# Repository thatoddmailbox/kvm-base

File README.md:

# kvm-base

The main board for the [open-source HDMI KVM switch I built](https://github.com/thatoddmailbox/kvm#kvm). Contains HDMI and USB switch ICs, allowing you to share two monitors and four USB devices between three different computers.

This is a 1.6mm four layer PCB, designed for JLCPCB's [JLC7628](https://jlcpcb.com/quote/pcbOrderFaq/PCB%20Stackup) impedance-controlled stackup. It most likely will not work (or will be limited in terms of HDMI performance) on another stackup.

It connects via a PS/2 cable to [kvm-keypad](https://github.com/thatoddmailbox/kvm-keypad)&mdash;however, it does _not_ use the actual PS/2 protocol.

Two [TMDS361B](https://www.ti.com/lit/ds/symlink/tmds361b.pdf) chips are used as HDMI switches, and an [FSUSB74](https://www.onsemi.com/pub/Collateral/FSUSB74-D.pdf) is used as the USB switch.

## Assembly
The full Bill of Materials is linked at the end of the README, and you should get the PCB fabricated at JLCPCB with their impedance-controlled JLC7628 process.

A stencil is probably the easiest way to assemble the board, but it's definitely possible to do so without one, as long as you have a hot air rework station. The trickiest parts to solder are probably the FSUSB74 (QFN with 0.4 mm pitch but no thermal pad) and the TMDS361B (TQFP with 0.5 mm pitch).

The HDMI connectors are also somewhat tricky, given that they are on both sides of the board and also have a relatively fine pitch. However, it's doable with a soldering iron, flux, solder wick, and ideally some form of magnification&mdash;you just have to be careful to ensure the pins are aligned with the footprint on the board before soldering.

## Note on sink-side output stages
Interestingly, the TMDS361B's datasheet pretty clearly states that it's "not intended for source side applications such as external switch boxes", which I probably missed when designing this board.

The consequences of this seem to be that there's little/no ESD protection on the sink side (the monitor output ports), and that the chip has a fairly weak sink-side output stage. That means you probably can't use the output with super long or super cheap cables. The inputs, however, should be fine, since TI claims that the TMDS361B has a "robust TMDS receive stage" that even works with out-of-spec HDMI signals.

Anecdotally, the output does seem to work, but I haven't tested it in that many conditions. This has been tested with a 3 foot HDMI cable going to an Acer EB243YU monitor, using a resolution of 2560 x 1440 at 75 Hz, which is outside of the TMDS361B's spec!

Theoretically, you might be able to work around this by running the output signals to another board with a retimer or redriver, but that's probably somewhat excessive. A future revision should use a different chip and/or integrate a retimer/redriver to the output stage. Unfortunately, it might be somewhat tricky to find an easily accessible HDMI switch chip&mdash;most seem to want you to sign an NDA before getting any documentation.

## Useful links
* [Rev A schematic](./mfg/revA/kvm-base.pdf)
* [Rev A BOM](./mfg/revA/kvm-base.csv)

## Known issues
* TMDS361B's sink-side output stages, as mentioned above
* HDMI ports are too close together -- some cables might be too big to fit
* Some FSUSB74 ports seem to not be working -- this could be a soldering issue
	* Port 2 works perfectly
	* With ports 0 and 1, the computer detects a device but then complains the device is not responding
	* Suspect that probably one of the D+/D- lines is not well connected
* The HPD and DDC lines are switched along with the ports. This means that switching ports will cause the connected source to think the monitor went away, which might not be what you want
	* A future version will probably need to have some sort of EDID cloning/emulation, or have some way to keep the HPD line high after the monitor is connected?
	* There is a workaround: cover the HPD pin (pin 19) of your HDMI cable with tape to block the HPD signal.
		* This workaround means that some sources, like a laptop, might not autodetect your HDMI cable. You'll need to have some way to rescan. On Linux, you can try the command `xrandr --listmonitors`.
		* This might be solvable by cutting the cable open and soldering a 10k resistor between HPD and +5V? That's somewhat extra though
* The device can kinda sorta be powered by a sink&mdash;most likely the ESD diodes in the TMDS361B are backfeeding power on the +5V line.
* The keypad might have some trouble with noise when a PS/2 cable is connected, although it has been worked around in the firmware. A future revision might need a buffer or redriver or something similar? Plain I2C is probably not the best choice for communication between the base and keypad.

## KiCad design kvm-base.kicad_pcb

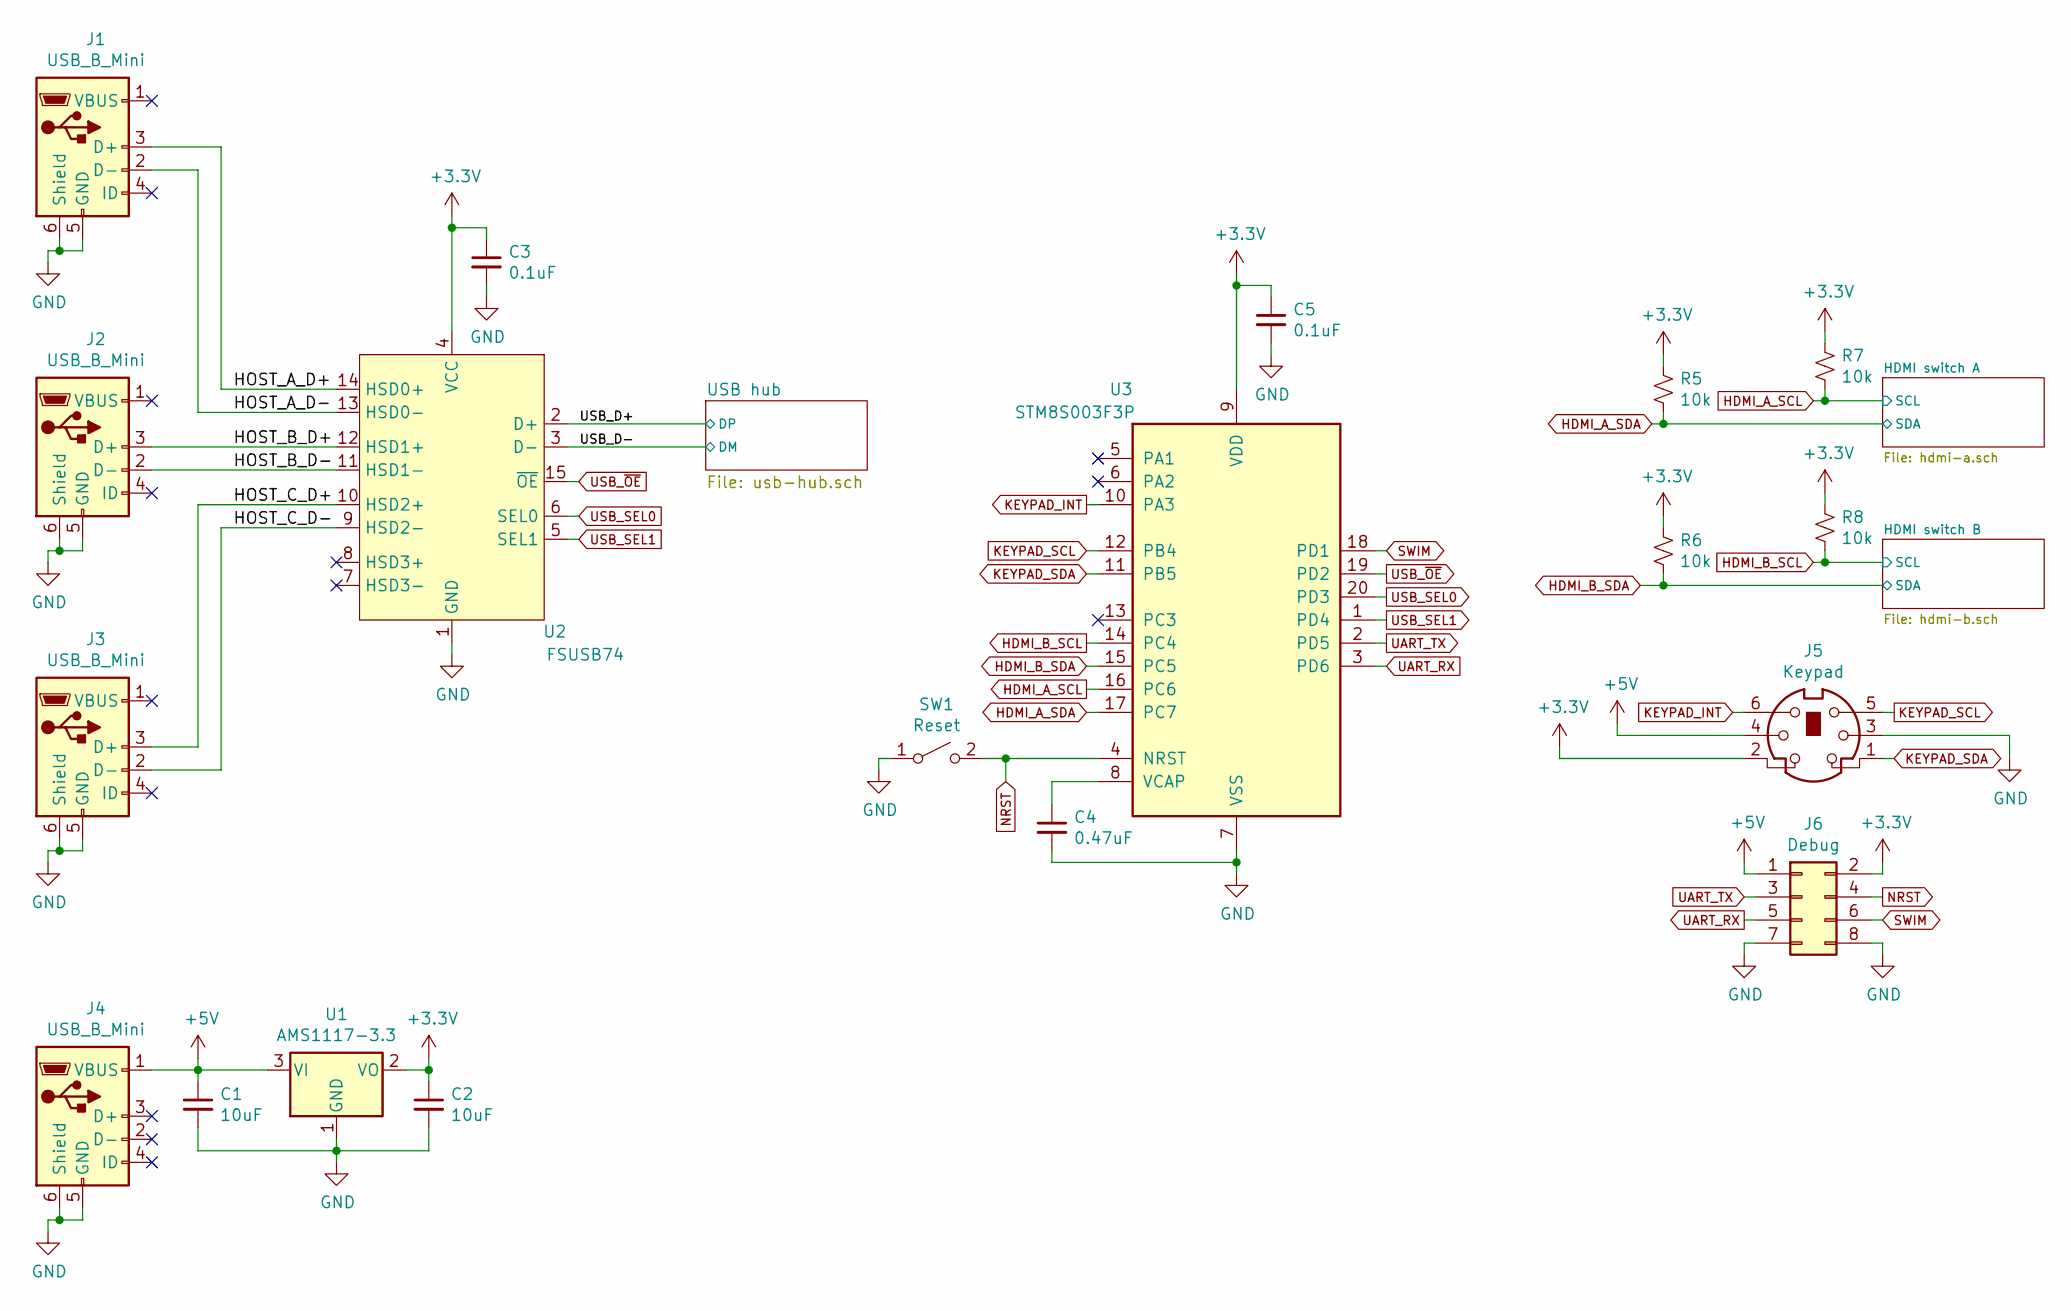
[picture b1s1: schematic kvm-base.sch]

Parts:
C1, C2: 10uF; C_0603_1608Metric_Pad1.05x0.95mm_HandSolder
C3, C5: 0.1uF; C_0603_1608Metric_Pad1.05x0.95mm_HandSolder
C4: 0.47uF; C_0603_1608Metric_Pad1.05x0.95mm_HandSolder
J1, J2, J3, J4: USB_B_Mini; USB_Mini-B_Lumberg_2486_01_Horizontal
J5: Keypad; PS2
J6: Debug; PinSocket_2x04_P2.54mm_Vertical
R5, R6, R7, R8: 10k; R_0603_1608Metric_Pad1.05x0.95mm_HandSolder
SW1: Reset; SW_Push_1P1T_NO_6x6mm_H9.5mm
U1: AMS1117-3.3; SOT-223-3_TabPin2
U2: FSUSB74; UMLP16
U3: STM8S003F3P; TSSOP-20_4.4x6.5mm_P0.65mm

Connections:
+3V3: C2.1, C3.1, C5.1, J5.2, J6.2, R5.1, R6.1, R7.1, R8.1, U1.2 (VO), U2.4 (VCC), U3.9 (VDD); also elsewhere on the board
+5V: C1.1, J4.1 (VBUS), J5.4, J6.1, U1.3 (VI); also elsewhere on the board
/HOST_A_D+: J1.3 (D+), U2.14 (HSD0+)
/HOST_A_D-: J1.2 (D-), U2.13 (HSD0-)
/HOST_B_D+: J2.3 (D+), U2.12 (HSD1+)
/HOST_B_D-: J2.2 (D-), U2.11 (HSD1-)
/HOST_C_D+: J3.3 (D+), U2.10 (HSD2+)
/HOST_C_D-: J3.2 (D-), U2.9 (HSD2-)
/USB_D+: U2.2 (D+); also elsewhere on the board
/USB_D-: U2.3 (D-); also elsewhere on the board
GND: C1.2, C2.2, C3.2, C4.2, C5.2, J1.5 (GND), J1.6 (Shield), J2.5 (GND), J2.6 (Shield), J3.5 (GND), J3.6 (Shield), J4.5 (GND), J4.6 (Shield), J5.3, J6.7, J6.8, SW1.1 (A), U1.1 (GND), U2.1 (GND), U3.7 (VSS); also elsewhere on the board
HDMI_A_SCL: R7.2, U3.16 (PC6); also elsewhere on the board
HDMI_A_SDA: R5.2, U3.17 (PC7); also elsewhere on the board
HDMI_B_SCL: R8.2, U3.14 (PC4); also elsewhere on the board
HDMI_B_SDA: R6.2, U3.15 (PC5); also elsewhere on the board
KEYPAD_INT: J5.6, U3.10 (PA3)
KEYPAD_SCL: J5.5, U3.12 (PB4)
KEYPAD_SDA: J5.1, U3.11 (PB5)
NRST: J6.4, SW1.2 (B), U3.4 (NRST)
unnamed: C4.1, U3.8 (VCAP)
SWIM: J6.6, U3.18 (PD1)
UART_RX: J6.5, U3.3 (PD6)
UART_TX: J6.3, U3.2 (PD5)
USB_SEL0: U2.6 (SEL0), U3.20 (PD3)
USB_SEL1: U2.5 (SEL1), U3.1 (PD4)
USB_~OE: U2.15 (~OE), U3.19 (PD2)

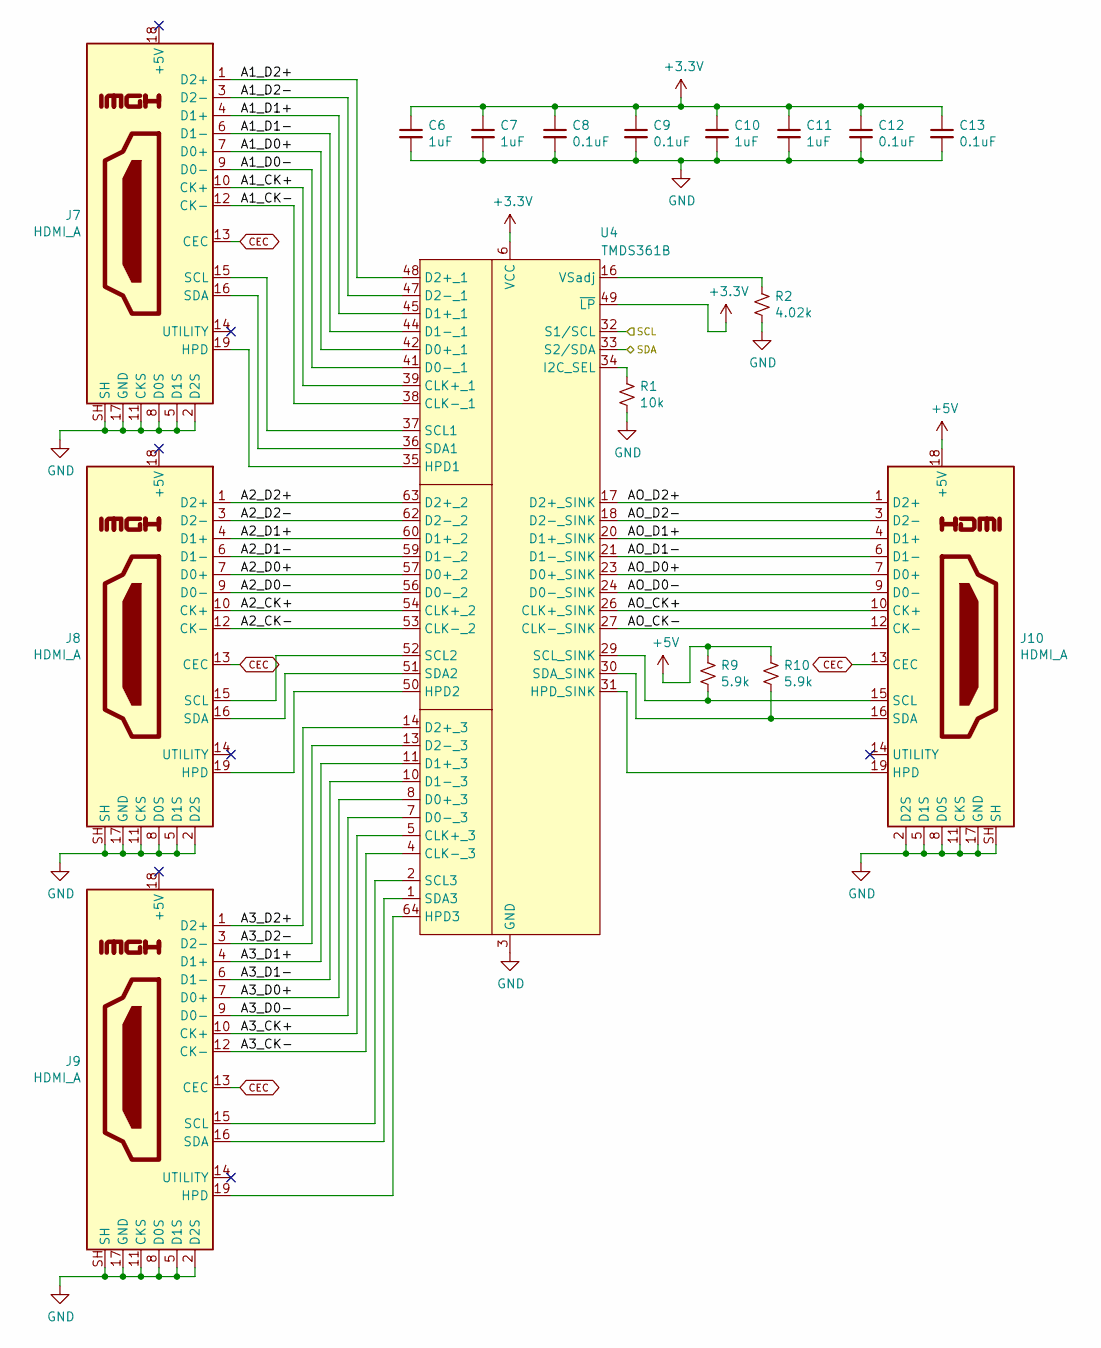
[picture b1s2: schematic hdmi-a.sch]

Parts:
C6, C7, C10, C11: 1uF; C_0603_1608Metric_Pad1.05x0.95mm_HandSolder
C8, C9, C12, C13: 0.1uF; C_0603_1608Metric_Pad1.05x0.95mm_HandSolder
J7, J8, J9, J10: HDMI_A; HDMI-001
R1: 10k; R_0603_1608Metric_Pad1.05x0.95mm_HandSolder
R2: 4.02k; R_0603_1608Metric_Pad1.05x0.95mm_HandSolder
R9, R10: 5.9k; R_0603_1608Metric_Pad1.05x0.95mm_HandSolder
U4: TMDS361B; LQFP-64_10x10mm_P0.5mm

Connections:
+3V3: C6.1, C7.1, C8.1, C9.1, C10.1, C11.1, C12.1, C13.1, U4.6 (VCC), U4.12 (VCC), U4.19 (VCC), U4.25 (VCC), U4.40 (VCC), U4.46 (VCC), U4.49 (~LP), U4.55 (VCC), U4.61 (VCC); also elsewhere on the board
+5V: J10.18 (+5V), R9.1, R10.1; also elsewhere on the board
/HDMI switch A/A1_CK+: J7.10 (CK+), U4.39 (CLK+_1)
/HDMI switch A/A1_CK-: J7.12 (CK-), U4.38 (CLK-_1)
/HDMI switch A/A1_D0+: J7.7 (D0+), U4.42 (D0+_1)
/HDMI switch A/A1_D0-: J7.9 (D0-), U4.41 (D0-_1)
/HDMI switch A/A1_D1+: J7.4 (D1+), U4.45 (D1+_1)
/HDMI switch A/A1_D1-: J7.6 (D1-), U4.44 (D1-_1)
/HDMI switch A/A1_D2+: J7.1 (D2+), U4.48 (D2+_1)
/HDMI switch A/A1_D2-: J7.3 (D2-), U4.47 (D2-_1)
/HDMI switch A/A2_CK+: J8.10 (CK+), U4.54 (CLK+_2)
/HDMI switch A/A2_CK-: J8.12 (CK-), U4.53 (CLK-_2)
/HDMI switch A/A2_D0+: J8.7 (D0+), U4.57 (D0+_2)
/HDMI switch A/A2_D0-: J8.9 (D0-), U4.56 (D0-_2)
/HDMI switch A/A2_D1+: J8.4 (D1+), U4.60 (D1+_2)
/HDMI switch A/A2_D1-: J8.6 (D1-), U4.59 (D1-_2)
/HDMI switch A/A2_D2+: J8.1 (D2+), U4.63 (D2+_2)
/HDMI switch A/A2_D2-: J8.3 (D2-), U4.62 (D2-_2)
/HDMI switch A/A3_CK+: J9.10 (CK+), U4.5 (CLK+_3)
/HDMI switch A/A3_CK-: J9.12 (CK-), U4.4 (CLK-_3)
/HDMI switch A/A3_D0+: J9.7 (D0+), U4.8 (D0+_3)
/HDMI switch A/A3_D0-: J9.9 (D0-), U4.7 (D0-_3)
/HDMI switch A/A3_D1+: J9.4 (D1+), U4.11 (D1+_3)
/HDMI switch A/A3_D1-: J9.6 (D1-), U4.10 (D1-_3)
/HDMI switch A/A3_D2+: J9.1 (D2+), U4.14 (D2+_3)
/HDMI switch A/A3_D2-: J9.3 (D2-), U4.13 (D2-_3)
/HDMI switch A/AO_CK+: J10.10 (CK+), U4.26 (CLK+_SINK)
/HDMI switch A/AO_CK-: J10.12 (CK-), U4.27 (CLK-_SINK)
/HDMI switch A/AO_D0+: J10.7 (D0+), U4.23 (D0+_SINK)
/HDMI switch A/AO_D0-: J10.9 (D0-), U4.24 (D0-_SINK)
/HDMI switch A/AO_D1+: J10.4 (D1+), U4.20 (D1+_SINK)
/HDMI switch A/AO_D1-: J10.6 (D1-), U4.21 (D1-_SINK)
/HDMI switch A/AO_D2+: J10.1 (D2+), U4.17 (D2+_SINK)
/HDMI switch A/AO_D2-: J10.3 (D2-), U4.18 (D2-_SINK)
CEC: J7.13 (CEC), J8.13 (CEC), J9.13 (CEC), J10.13 (CEC); also elsewhere on the board
GND: C6.2, C7.2, C8.2, C9.2, C10.2, C11.2, C12.2, C13.2, J7.2 (D2S), J7.5 (D1S), J7.8 (D0S), J7.11 (CKS), J7.17 (GND), J7.SH, J8.2 (D2S), J8.5 (D1S), J8.8 (D0S), J8.11 (CKS), J8.17 (GND), J8.SH, J9.2 (D2S), J9.5 (D1S), J9.8 (D0S), J9.11 (CKS), J9.17 (GND), J9.SH, J10.2 (D2S), J10.5 (D1S), J10.8 (D0S), J10.11 (CKS), J10.17 (GND), J10.SH, R1.2, R2.2, U4.3 (GND), U4.9 (GND), U4.15 (GND), U4.22 (GND), U4.28 (GND), U4.43 (GND), U4.58 (GND); also elsewhere on the board
HDMI_A_SCL: U4.32 (S1/SCL); also elsewhere on the board
HDMI_A_SDA: U4.33 (S2/SDA); also elsewhere on the board
unnamed: J7.15 (SCL), U4.37 (SCL1)
unnamed: J7.16 (SDA), U4.36 (SDA1)
unnamed: J7.19 (HPD), U4.35 (HPD1)
unnamed: J8.15 (SCL), U4.52 (SCL2)
unnamed: J8.16 (SDA), U4.51 (SDA2)
unnamed: J8.19 (HPD), U4.50 (HPD2)
unnamed: J9.15 (SCL), U4.2 (SCL3)
unnamed: J9.16 (SDA), U4.1 (SDA3)
unnamed: J9.19 (HPD), U4.64 (HPD3)
unnamed: J10.15 (SCL), R9.2, U4.29 (SCL_SINK)
unnamed: J10.16 (SDA), R10.2, U4.30 (SDA_SINK)
unnamed: J10.19 (HPD), U4.31 (HPD_SINK)
unnamed: R1.1, U4.34 (I2C_SEL)
unnamed: R2.1, U4.16 (VSadj)

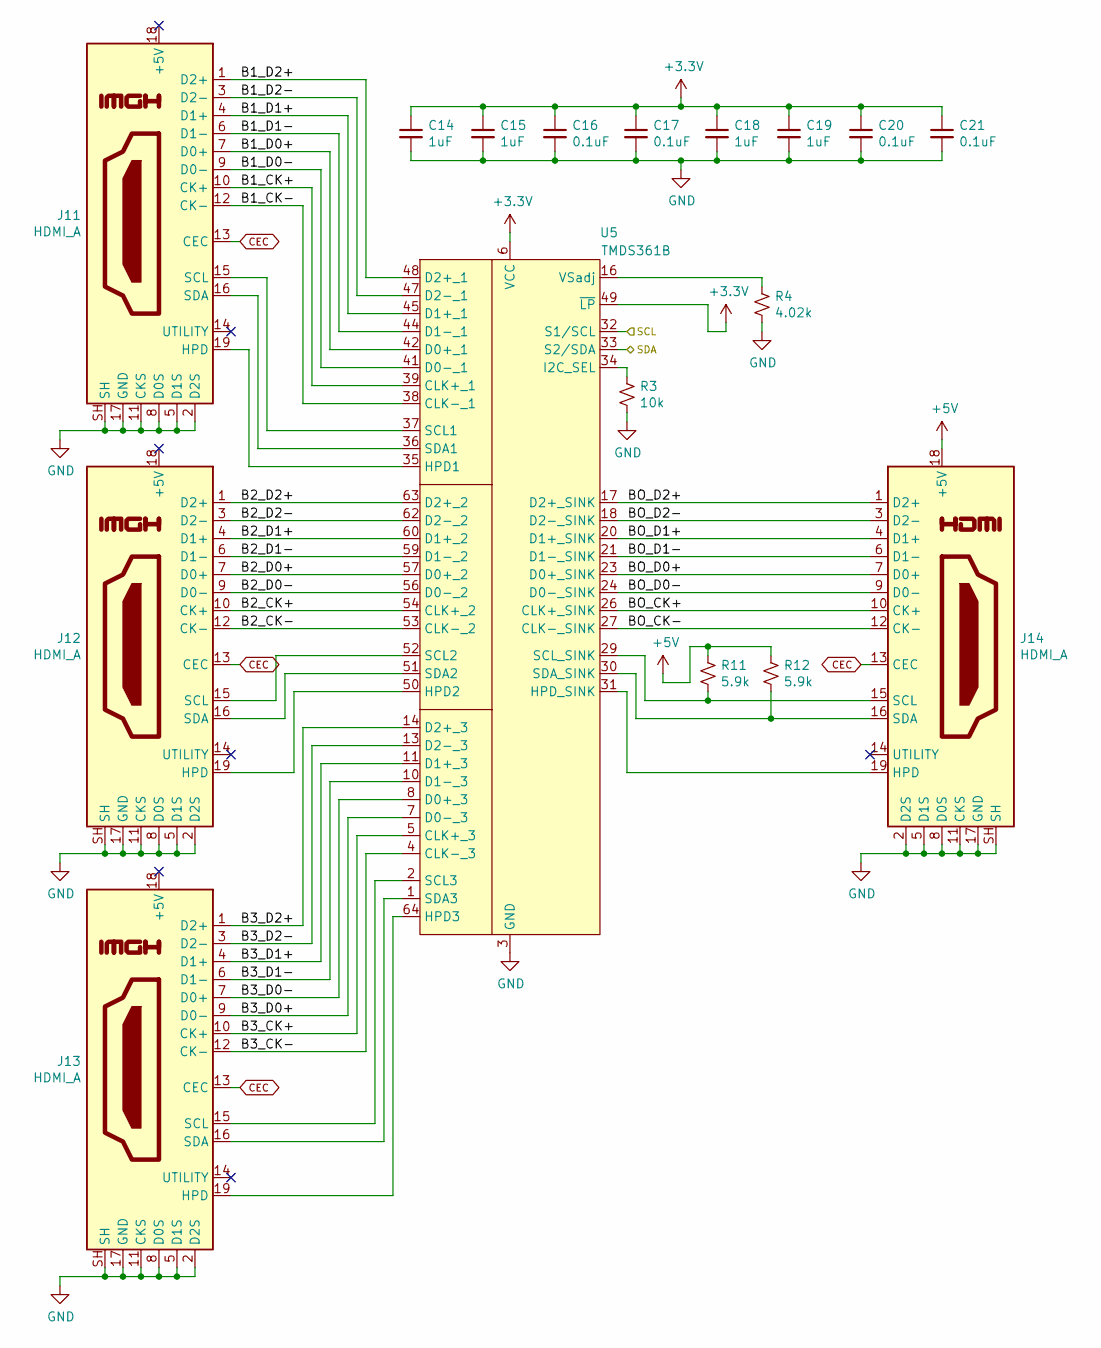
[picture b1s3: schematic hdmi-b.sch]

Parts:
C14, C15, C18, C19: 1uF; C_0603_1608Metric_Pad1.05x0.95mm_HandSolder
C16, C17, C20, C21: 0.1uF; C_0603_1608Metric_Pad1.05x0.95mm_HandSolder
J11, J12, J13, J14: HDMI_A; HDMI-001
R3: 10k; R_0603_1608Metric_Pad1.05x0.95mm_HandSolder
R4: 4.02k; R_0603_1608Metric_Pad1.05x0.95mm_HandSolder
R11, R12: 5.9k; R_0603_1608Metric_Pad1.05x0.95mm_HandSolder
U5: TMDS361B; LQFP-64_10x10mm_P0.5mm

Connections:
+3V3: C14.1, C15.1, C16.1, C17.1, C18.1, C19.1, C20.1, C21.1, U5.6 (VCC), U5.12 (VCC), U5.19 (VCC), U5.25 (VCC), U5.40 (VCC), U5.46 (VCC), U5.49 (~LP), U5.55 (VCC), U5.61 (VCC); also elsewhere on the board
+5V: J14.18 (+5V), R11.1, R12.1; also elsewhere on the board
/HDMI switch B/B1_CK+: J11.10 (CK+), U5.39 (CLK+_1)
/HDMI switch B/B1_CK-: J11.12 (CK-), U5.38 (CLK-_1)
/HDMI switch B/B1_D0+: J11.7 (D0+), U5.42 (D0+_1)
/HDMI switch B/B1_D0-: J11.9 (D0-), U5.41 (D0-_1)
/HDMI switch B/B1_D1+: J11.4 (D1+), U5.45 (D1+_1)
/HDMI switch B/B1_D1-: J11.6 (D1-), U5.44 (D1-_1)
/HDMI switch B/B1_D2+: J11.1 (D2+), U5.48 (D2+_1)
/HDMI switch B/B1_D2-: J11.3 (D2-), U5.47 (D2-_1)
/HDMI switch B/B2_CK+: J12.10 (CK+), U5.54 (CLK+_2)
/HDMI switch B/B2_CK-: J12.12 (CK-), U5.53 (CLK-_2)
/HDMI switch B/B2_D0+: J12.7 (D0+), U5.57 (D0+_2)
/HDMI switch B/B2_D0-: J12.9 (D0-), U5.56 (D0-_2)
/HDMI switch B/B2_D1+: J12.4 (D1+), U5.60 (D1+_2)
/HDMI switch B/B2_D1-: J12.6 (D1-), U5.59 (D1-_2)
/HDMI switch B/B2_D2+: J12.1 (D2+), U5.63 (D2+_2)
/HDMI switch B/B2_D2-: J12.3 (D2-), U5.62 (D2-_2)
/HDMI switch B/B3_CK+: J13.10 (CK+), U5.5 (CLK+_3)
/HDMI switch B/B3_CK-: J13.12 (CK-), U5.4 (CLK-_3)
/HDMI switch B/B3_D0+: J13.9 (D0-), U5.7 (D0-_3)
/HDMI switch B/B3_D0-: J13.7 (D0+), U5.8 (D0+_3)
/HDMI switch B/B3_D1+: J13.4 (D1+), U5.11 (D1+_3)
/HDMI switch B/B3_D1-: J13.6 (D1-), U5.10 (D1-_3)
/HDMI switch B/B3_D2+: J13.1 (D2+), U5.14 (D2+_3)
/HDMI switch B/B3_D2-: J13.3 (D2-), U5.13 (D2-_3)
/HDMI switch B/BO_CK+: J14.10 (CK+), U5.26 (CLK+_SINK)
/HDMI switch B/BO_CK-: J14.12 (CK-), U5.27 (CLK-_SINK)
/HDMI switch B/BO_D0+: J14.7 (D0+), U5.23 (D0+_SINK)
/HDMI switch B/BO_D0-: J14.9 (D0-), U5.24 (D0-_SINK)
/HDMI switch B/BO_D1+: J14.4 (D1+), U5.20 (D1+_SINK)
/HDMI switch B/BO_D1-: J14.6 (D1-), U5.21 (D1-_SINK)
/HDMI switch B/BO_D2+: J14.1 (D2+), U5.17 (D2+_SINK)
/HDMI switch B/BO_D2-: J14.3 (D2-), U5.18 (D2-_SINK)
CEC: J11.13 (CEC), J12.13 (CEC), J13.13 (CEC), J14.13 (CEC); also elsewhere on the board
GND: C14.2, C15.2, C16.2, C17.2, C18.2, C19.2, C20.2, C21.2, J11.2 (D2S), J11.5 (D1S), J11.8 (D0S), J11.11 (CKS), J11.17 (GND), J11.SH, J12.2 (D2S), J12.5 (D1S), J12.8 (D0S), J12.11 (CKS), J12.17 (GND), J12.SH, J13.2 (D2S), J13.5 (D1S), J13.8 (D0S), J13.11 (CKS), J13.17 (GND), J13.SH, J14.2 (D2S), J14.5 (D1S), J14.8 (D0S), J14.11 (CKS), J14.17 (GND), J14.SH, R3.2, R4.2, U5.3 (GND), U5.9 (GND), U5.15 (GND), U5.22 (GND), U5.28 (GND), U5.43 (GND), U5.58 (GND); also elsewhere on the board
HDMI_B_SCL: U5.32 (S1/SCL); also elsewhere on the board
HDMI_B_SDA: U5.33 (S2/SDA); also elsewhere on the board
unnamed: J11.15 (SCL), U5.37 (SCL1)
unnamed: J11.16 (SDA), U5.36 (SDA1)
unnamed: J11.19 (HPD), U5.35 (HPD1)
unnamed: J12.15 (SCL), U5.52 (SCL2)
unnamed: J12.16 (SDA), U5.51 (SDA2)
unnamed: J12.19 (HPD), U5.50 (HPD2)
unnamed: J13.15 (SCL), U5.2 (SCL3)
unnamed: J13.16 (SDA), U5.1 (SDA3)
unnamed: J13.19 (HPD), U5.64 (HPD3)
unnamed: J14.15 (SCL), R11.2, U5.29 (SCL_SINK)
unnamed: J14.16 (SDA), R12.2, U5.30 (SDA_SINK)
unnamed: J14.19 (HPD), U5.31 (HPD_SINK)
unnamed: R3.1, U5.34 (I2C_SEL)
unnamed: R4.1, U5.16 (VSadj)

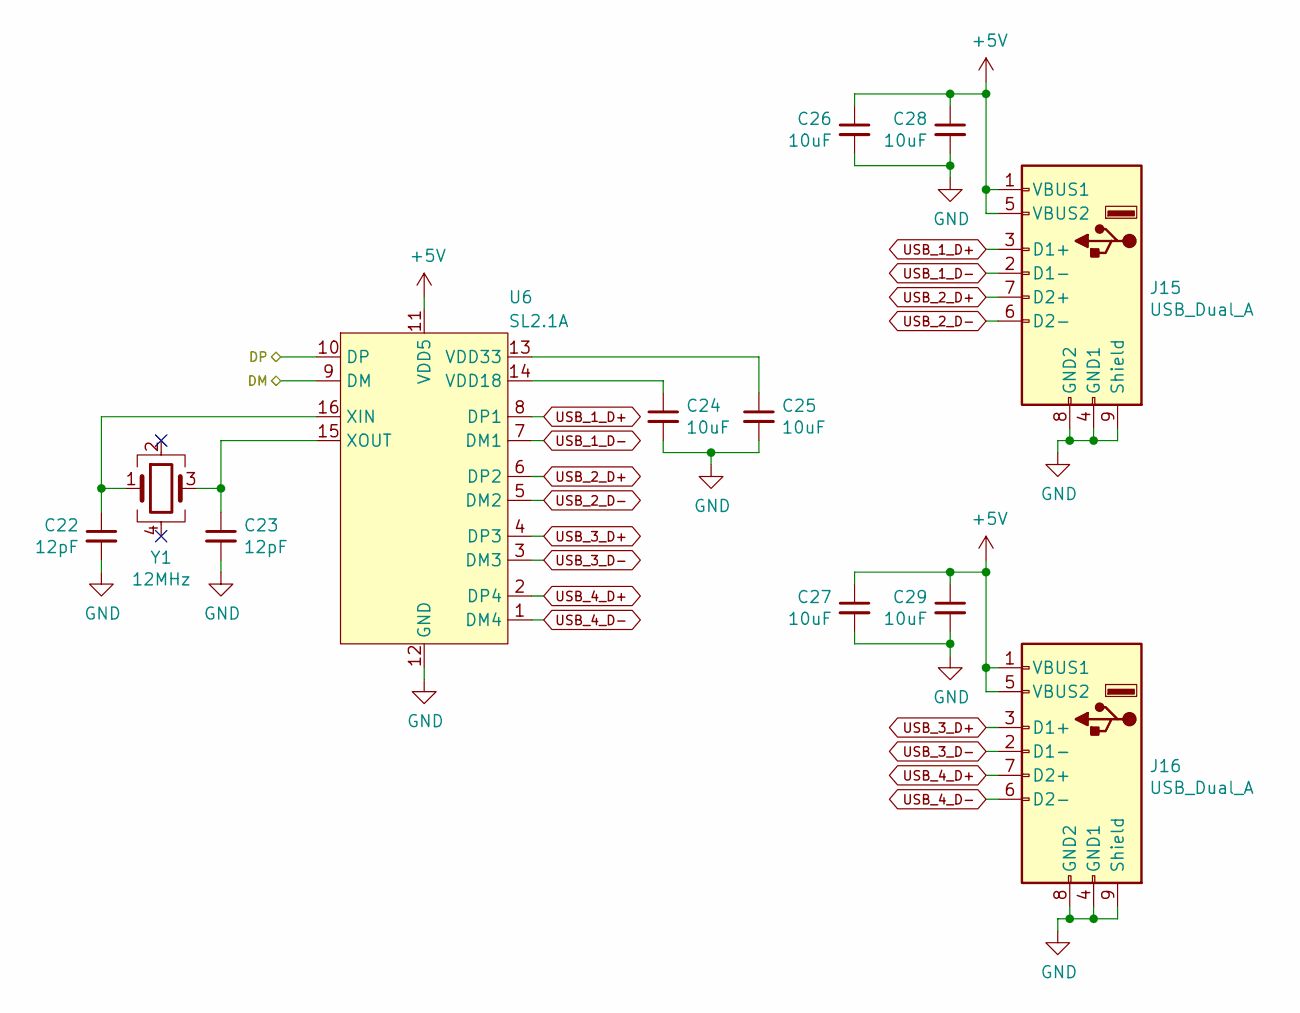
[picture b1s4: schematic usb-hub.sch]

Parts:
C22, C23: 12pF; C_0603_1608Metric_Pad1.05x0.95mm_HandSolder
C24, C25, C26, C27, C28, C29: 10uF; C_0603_1608Metric_Pad1.05x0.95mm_HandSolder
J15, J16: USB_Dual_A; USB_A_Wuerth_61400826021_Horizontal_Stacked
U6: SL2.1A; SOIC-16_3.9x9.9mm_P1.27mm
Y1: 12MHz; Crystal_SMD_3225-4Pin_3.2x2.5mm_HandSoldering

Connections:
+5V: C26.1, C27.1, C28.1, C29.1, J15.1 (VBUS1), J15.5 (VBUS2), J16.1 (VBUS1), J16.5 (VBUS2), U6.11 (VDD5); also elsewhere on the board
/USB_D+: U6.10 (DP); also elsewhere on the board
/USB_D-: U6.9 (DM); also elsewhere on the board
GND: C22.2, C23.2, C24.2, C25.2, C26.2, C27.2, C28.2, C29.2, J15.4 (GND1), J15.8 (GND2), J15.9 (Shield), J16.4 (GND1), J16.8 (GND2), J16.9 (Shield), U6.12 (GND); also elsewhere on the board
unnamed: C22.1, U6.16 (XIN), Y1.1
unnamed: C23.1, U6.15 (XOUT), Y1.3
unnamed: C24.1, U6.14 (VDD18)
unnamed: C25.1, U6.13 (VDD33)
USB_1_D+: J15.3 (D1+), U6.8 (DP1)
USB_1_D-: J15.2 (D1-), U6.7 (DM1)
USB_2_D+: J15.7 (D2+), U6.6 (DP2)
USB_2_D-: J15.6 (D2-), U6.5 (DM2)
USB_3_D+: J16.3 (D1+), U6.4 (DP3)
USB_3_D-: J16.2 (D1-), U6.3 (DM3)
USB_4_D+: J16.7 (D2+), U6.2 (DP4)
USB_4_D-: J16.6 (D2-), U6.1 (DM4)

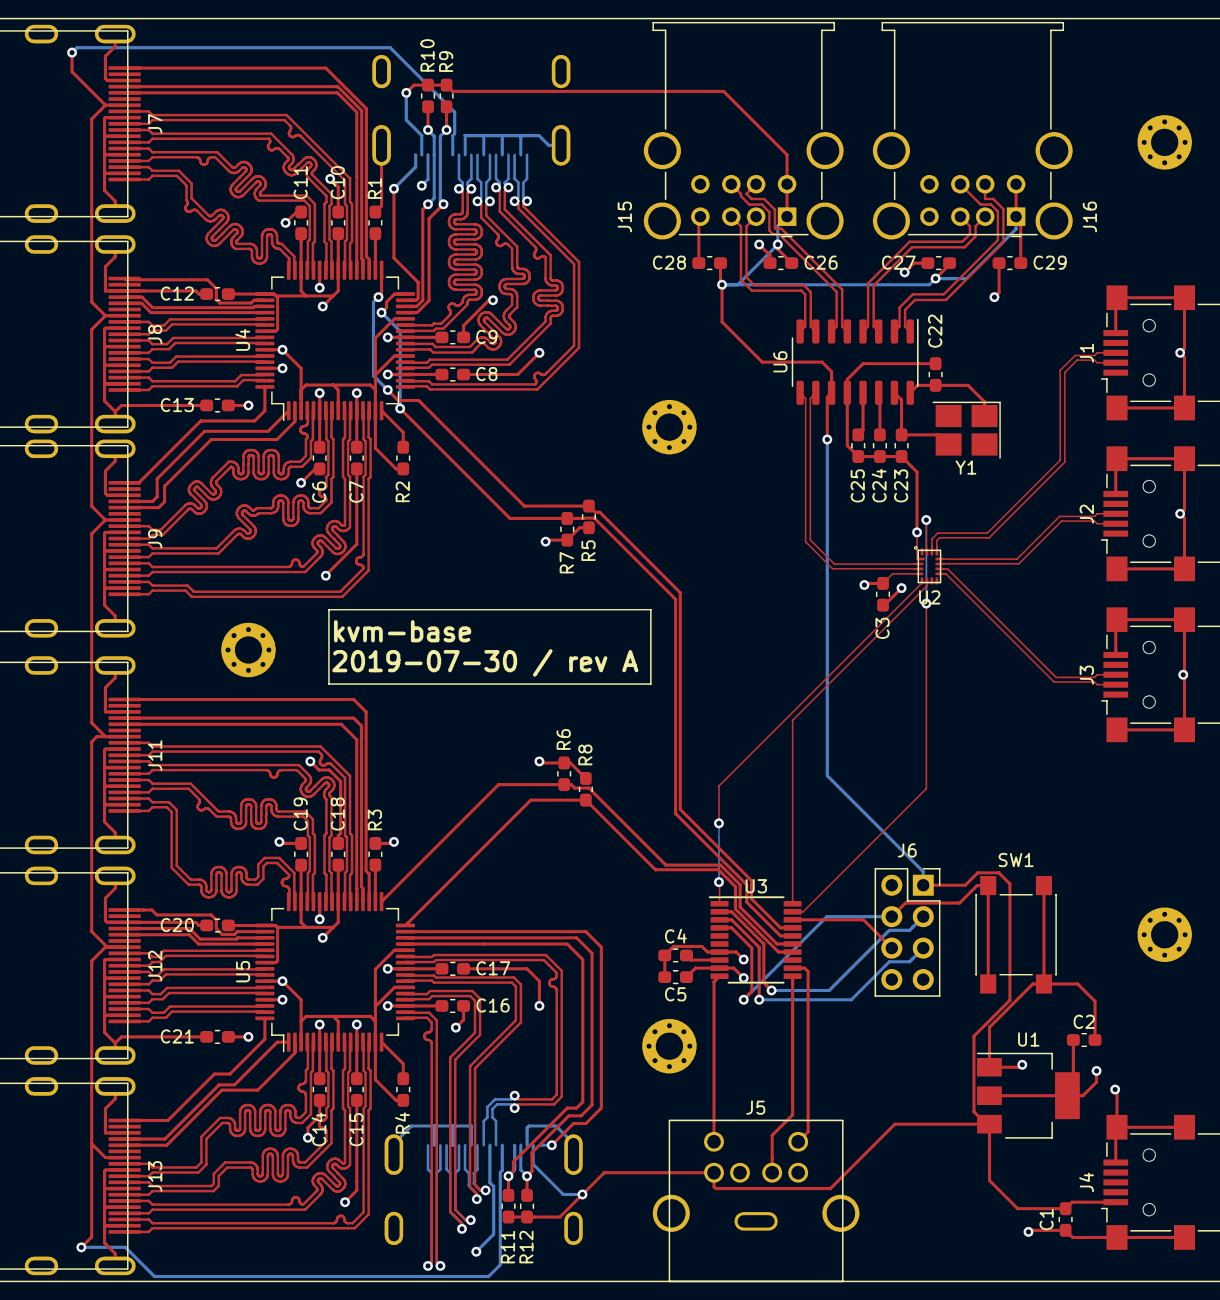
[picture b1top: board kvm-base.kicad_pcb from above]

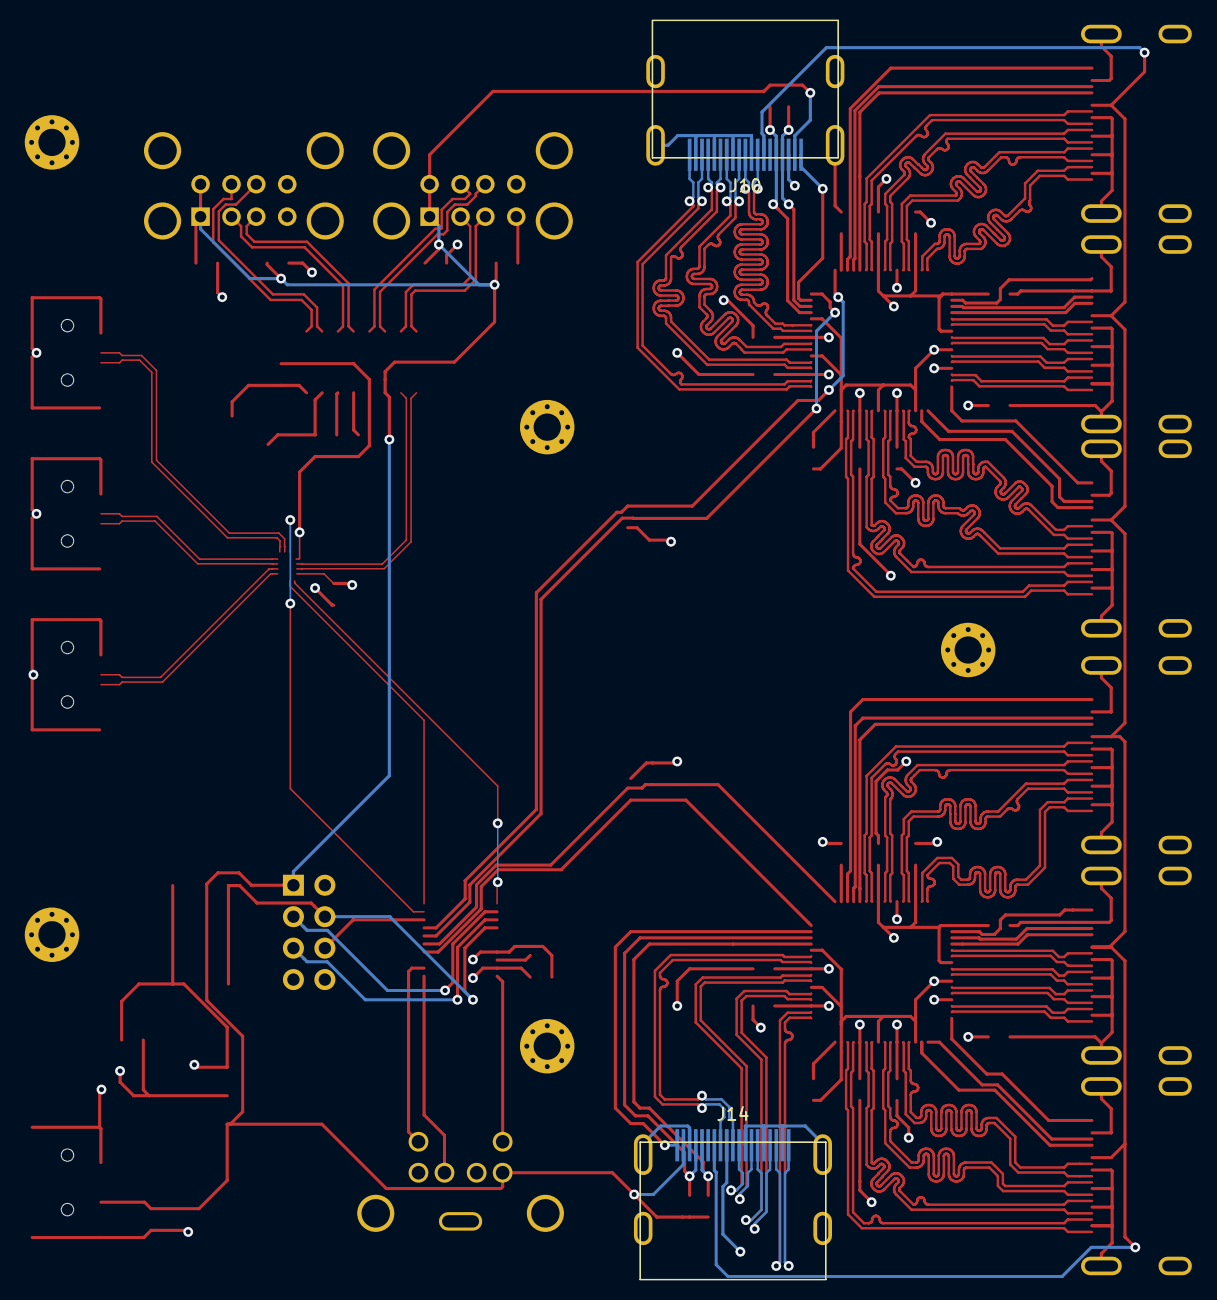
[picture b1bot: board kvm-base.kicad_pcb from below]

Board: 4 copper layers, 65 parts (2 on the bottom side), 131 nets.

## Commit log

2019-07-30 commit rev A schematic, pcb, and gerbers
2021-02-04 add README
2021-02-04 readme: add a description
2021-02-04 readme: add note about ps/2 cable
2021-02-04 readme: link to keypad repo
2021-02-04 readme: clarify that the ps/2 protocol is not used
2021-02-04 add csv bom file for rev A
2021-02-04 readme: add links to schematic and bom
2021-02-12 readme: link to the parts used
2021-02-12 readme: lol whoops
2021-02-12 readme: talk about output stage of tmds361b
2021-02-12 readme: add note about inputs
2021-02-12 readme: could use retimer/redriver
2021-02-12 readme: add note about search for other chips
2021-02-12 readme: move all the stuff about the tmds361b's output stage to a separate section
2021-02-12 readme: mention the stackup used
2021-02-12 readme: link to stackup and mention board thickness
2021-02-12 readme: add notes about assembly
2021-02-12 readme: grammar fix
2021-02-12 readme: add note on hdmi connector assembly
2021-02-12 readme: you also need some magnifier to assemble the hdmi connectors
2021-02-12 readme: add note about bom and pcb
2021-02-16 readme: add known issues section
2021-02-16 readme: add another issue
2021-02-16 readme: add yet another issue
2021-02-16 readme: add troubleshooting info for fsub74 info
2021-02-16 readme: add more info about fsusb74 issue
2021-02-22 add LICENSE
2021-03-07 readme: add known issue about hpd and edid
2021-03-07 readme: add hpd workaround
2021-03-07 readme: add linux xrandr command
2021-03-07 readme: add another workaround idea for hpd issue
2021-03-07 readme: usb ports are not working :(
2021-03-07 readme: this literally was already there and i missed it
2021-03-07 readme: mention that the output kinda sorta works
2021-03-07 readme: mention tested cable length and monitor
2021-03-07 readme: add resolution
2021-03-07 readme: mention that the resolution is actually out of spec technically
2021-03-08 readme: add note about ESD diodes backfeeding power
2021-03-08 readme: add note about keypad ps/2 noise issues
2021-03-08 readme: mention weirdness of ps/2 noise issues
2021-03-08 readme: changes about ps/2 noise issues
2021-03-18 readme: add missing space
2021-03-24 readme: tweak first line
2021-03-24 readme: link to main kvm repo
2021-03-24 readme: make first line link consistent
2021-04-14 readme: add more details to known issue
2021-04-14 readme: use the proper term DDC instead of I2C
2021-04-14 readme: add image
